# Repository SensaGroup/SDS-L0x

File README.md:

# SDS-L0x
Sensa Detection System - L0x v1.0

## Sponsored by AISLER
### Develop and manufacture your own premium boards at [aisler.net](https://aisler.net/)

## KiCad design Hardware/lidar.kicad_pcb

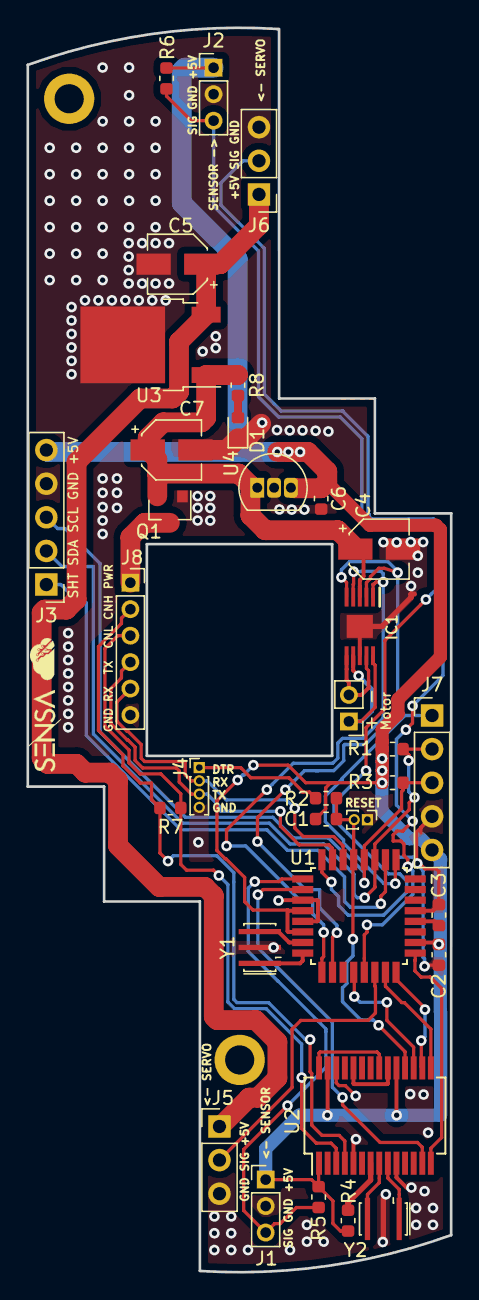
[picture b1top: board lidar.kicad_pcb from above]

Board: 2 copper layers, 32.0 x 94.0 mm, 34 parts (0 on the bottom side), 37 nets.

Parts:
C1, C2, C3, C6: 0.1uF; C_0603_1608Metric
C4, C5, C7: CP; CP_Elec_4x5.8
D1: LED; LED_0603_1608Metric
IC1: A3909GLYTR-T; SOP50P488X115-11N
J1: SENSOR1; PinHeader_1x03_P2.00mm_Vertical
J2: SENSOR2; PinHeader_1x03_P2.00mm_Vertical
J3: VL53L0X_1; PinHeader_1x05_P2.54mm_Vertical
J4: programming; PinHeader_1x04_P1.00mm_Vertical
J5: SERVO1; PinHeader_1x03_P2.54mm_Vertical
J6: SERVO2; PinHeader_1x03_P2.54mm_Vertical
J7: VL53L0X_2; PinHeader_1x05_P2.54mm_Vertical
J8: Main conn; PinSocket_1x06_P2.00mm_Vertical
J9: Motor; PinHeader_1x02_P2.00mm_Vertical
Q1: DMP2100U; SOT-23
R1, R3: 4K7; R_0603_1608Metric
R2, R4, R5, R6: 10K; R_0603_1608Metric
R7: 120; R_0603_1608Metric
R8: 1K; R_0603_1608Metric
SW1: Reset; PinHeader_1x02_P1.00mm_Vertical
U1: ATmega328P-AU; TQFP-32_7x7mm_P0.8mm
U2: MCP25625-x-SS; SSOP-28_5.3x10.2mm_P0.65mm
U3: L7806; TO-252-2
U4: L4931; TO-92L_Inline
Y1, Y2: 16MHz resonator; Resonator_SMD_muRata_CSTxExxV-3Pin_3.0x1.1mm_HandSoldering

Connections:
+5V: C2.1, C6.2, J1.1, J2.1, J3.5, J7.5, R1.1, R2.1, R3.1, R4.2, R5.2, R6.2, U1.4, U1.6, U1.18, U2.1, U2.19, U2.27, U4.3
CANH: J8.2, R7.2, U2.4
CANL: J8.3, R7.1, U2.3
D4: U1.2, U2.13
D8: U1.12, U2.17
DC_IN1: IC1.1, IC1.4, U1.9
DC_IN2: IC1.2, IC1.5, U1.10
DTR: C1.2, J4.1
GND: C2.2, C3.2, C4.2, C5.2, C6.1, C7.2, D1.1, IC1.8, IC1.11, J1.2, J2.2, J3.4, J4.4, J5.3, J6.3, J7.4, J8.6, Q1.1, SW1.1, U1.3, U1.5, U1.21, U2.5, U2.10, U2.26, U3.2, U4.2, Y1.2, Y2.2
MISO: U1.16, U2.16
MOSI: U1.15, U2.15
unnamed: C3.1, U1.20
unnamed: D1.2, R8.2
unnamed: IC1.6, IC1.9, J9.2
unnamed: IC1.7, IC1.10, J9.1
unnamed: J8.1, Q1.3
unnamed: R4.1, U2.7
unnamed: U1.7, Y1.3
unnamed: U1.8, Y1.1
unnamed: U2.8, Y2.3
unnamed: U2.9, Y2.1
unnamed: U2.20, U2.24
unnamed: U2.21, U2.28
RESET: C1.1, R2.2, SW1.2, U1.29, U2.18
RX: J4.2, J8.5, U1.30
SCK: U1.17, U2.14
SCL: J3.3, J7.3, R3.2, U1.28
SDA: J3.2, J7.2, R1.2, U1.27
SENSOR_1: J1.3, R5.1, U1.1
SENSOR_2: J2.3, R6.1, U1.32
SERVO_1: J5.2, U1.14
SERVO_2: J6.2, U1.13
SERVO_VCC: C5.1, J5.1, J6.1, U3.3
TX: J4.3, J8.4, U1.31
VCC: C4.1, C7.1, IC1.3, Q1.2, R8.1, U3.1, U4.1
VL1_XSHUT: J3.1, U1.26
VL2_XSHUT: J7.1, U1.25

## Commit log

2019-01-04 Added hardware, first bit
2019-01-10 Changed digikey link on u3
2019-01-10 Cleanup, generated schematic
2019-01-10 Added view.png
2019-01-10 Small readme update
2019-01-10 README update
2019-03-28 Added software and gitignore
